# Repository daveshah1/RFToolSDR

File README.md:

# RFTool AD9361 based SDR
RFTool is a standalone AD9361 based SDR with a USB 3 interface and a number of other useful features:

 - AD9361 transceiver IC - dual channel 70MHz-6GHz, up to 54MHz channel bandwidth
 - Xilinx Artix-7 FPGA (XC7A50T-2FTG256I) with 64MBit HyperRAM
 - FT601Q USB 3.0 interface
 - Two LNA inputs (500MHz-3GHz only) and one attenuated input (full AD9361 range)
 - All inputs protected to over +27dBm input
 - Two PA outputs (500MHz-3GHz only) with >20dBm output power and one direct output (full range)
 - Flexible external reference input (switchable termination and coupling)
 - USB powered, no external power needed

Rev 1.0 of the hardware has been built and initial tests completed. Receive-only
FPGA code and a simple Spectrum Analyser application for Linux has also been built.

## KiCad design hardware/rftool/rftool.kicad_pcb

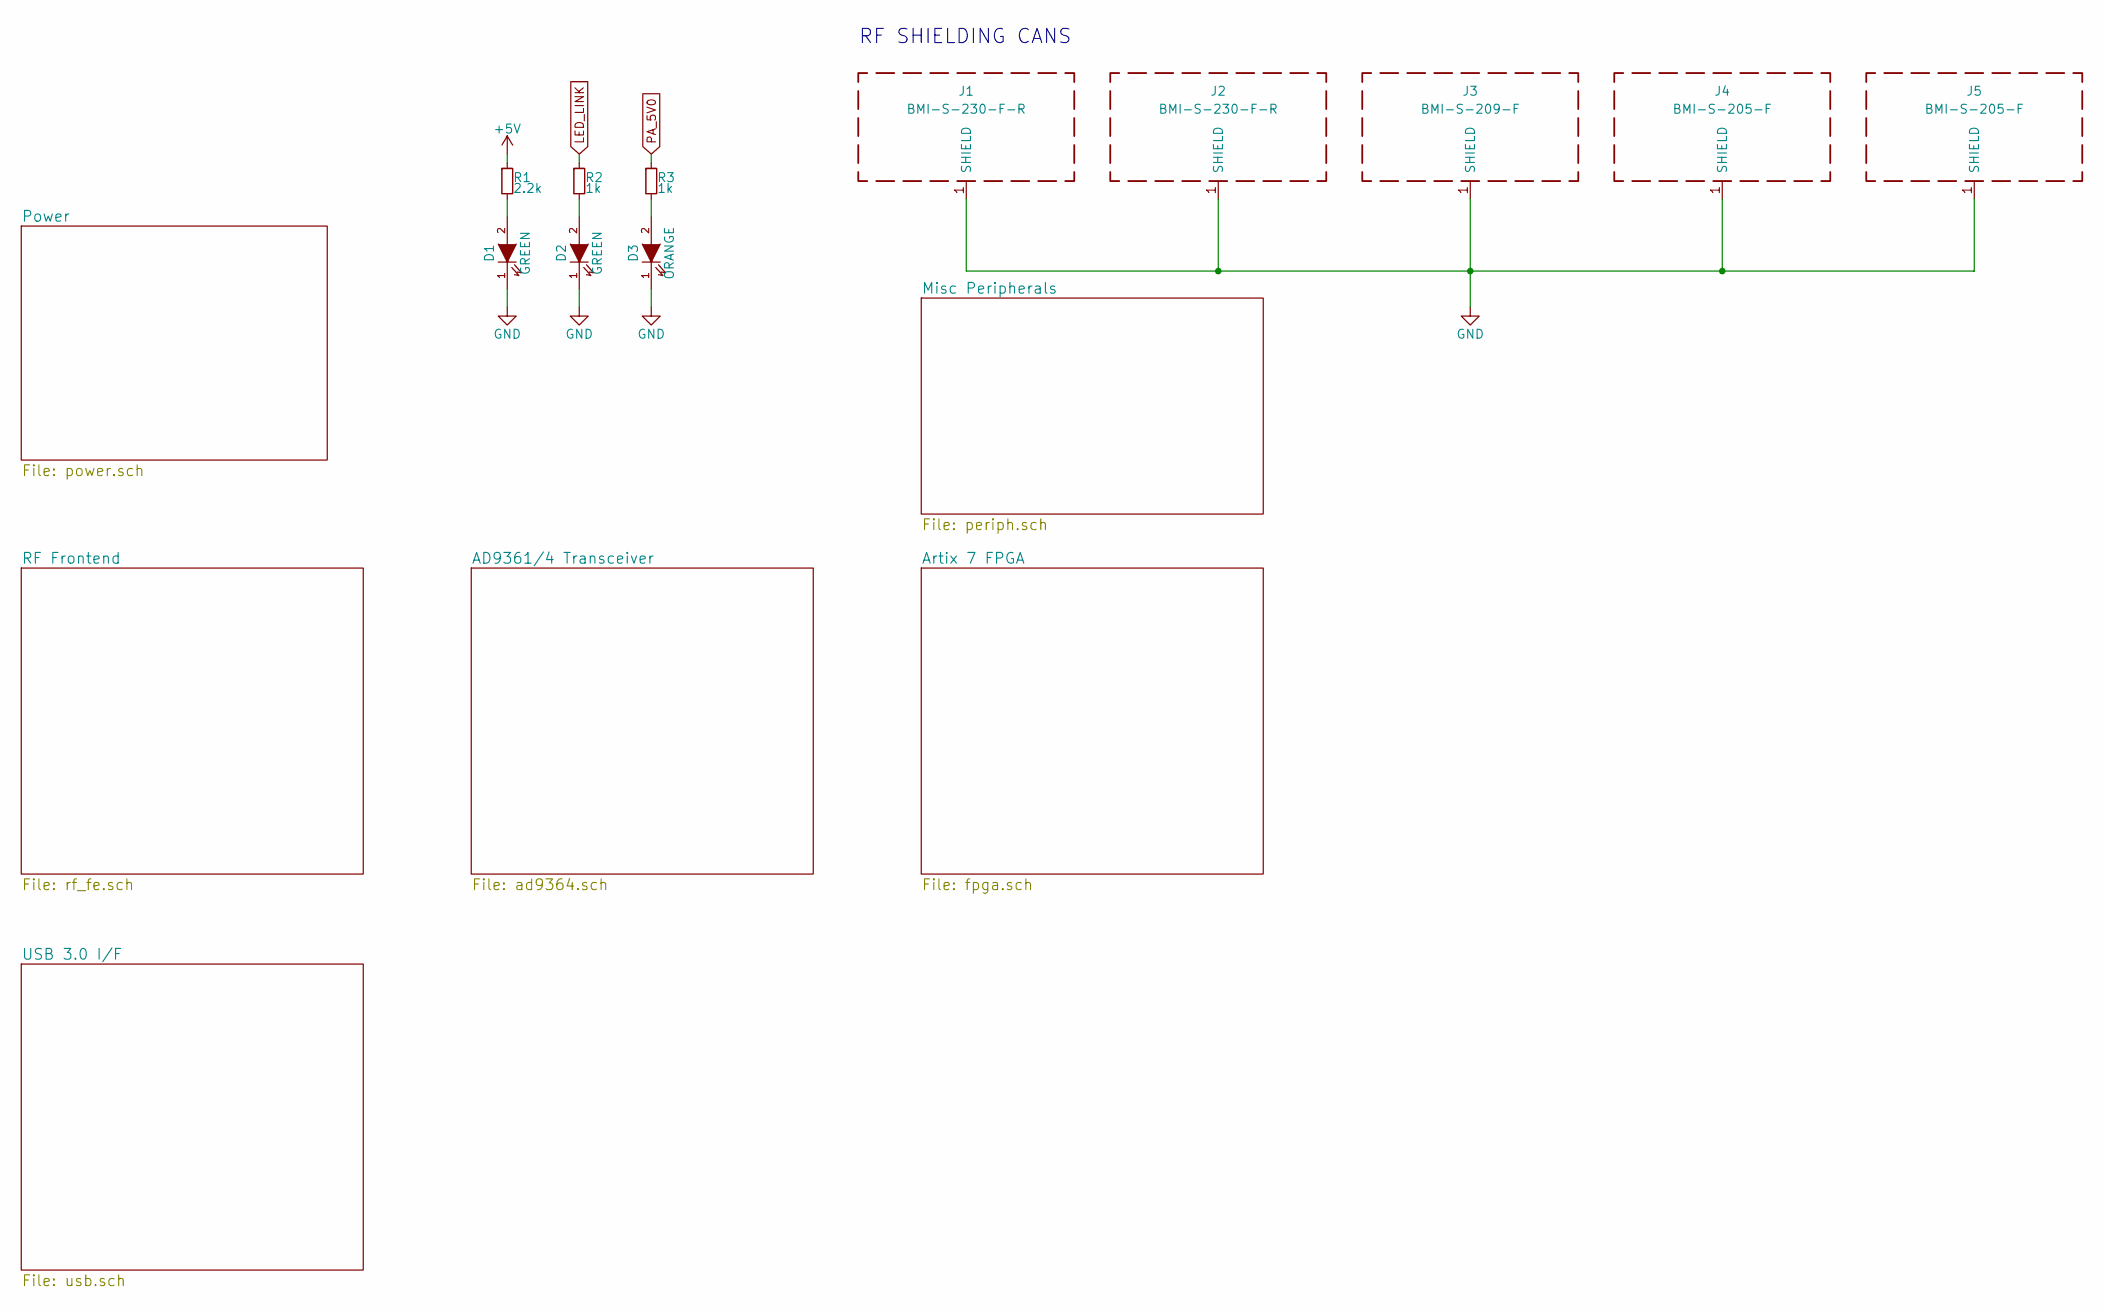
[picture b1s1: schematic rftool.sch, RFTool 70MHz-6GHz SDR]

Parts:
D1, D2: GREEN; LED_0805
D3: ORANGE; LED_0805
J1, J2: BMI-S-230-F-R
J3: BMI-S-209-F
J4, J5: BMI-S-205-F
R1: 2.2k; R_0402
R2, R3: 1k; R_0402

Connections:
+5V: R1.1; also elsewhere on the board
GND: D1.1 (K), D2.1 (K), D3.1 (K), J1.1, J2.1, J3.1, J4.1, J5.1; also elsewhere on the board
LED_LINK: R2.1; also elsewhere on the board
unnamed: D1.2 (A), R1.2
unnamed: D2.2 (A), R2.2
unnamed: D3.2 (A), R3.2
PA_5V0: R3.1; also elsewhere on the board

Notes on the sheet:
RF SHIELDING CANS

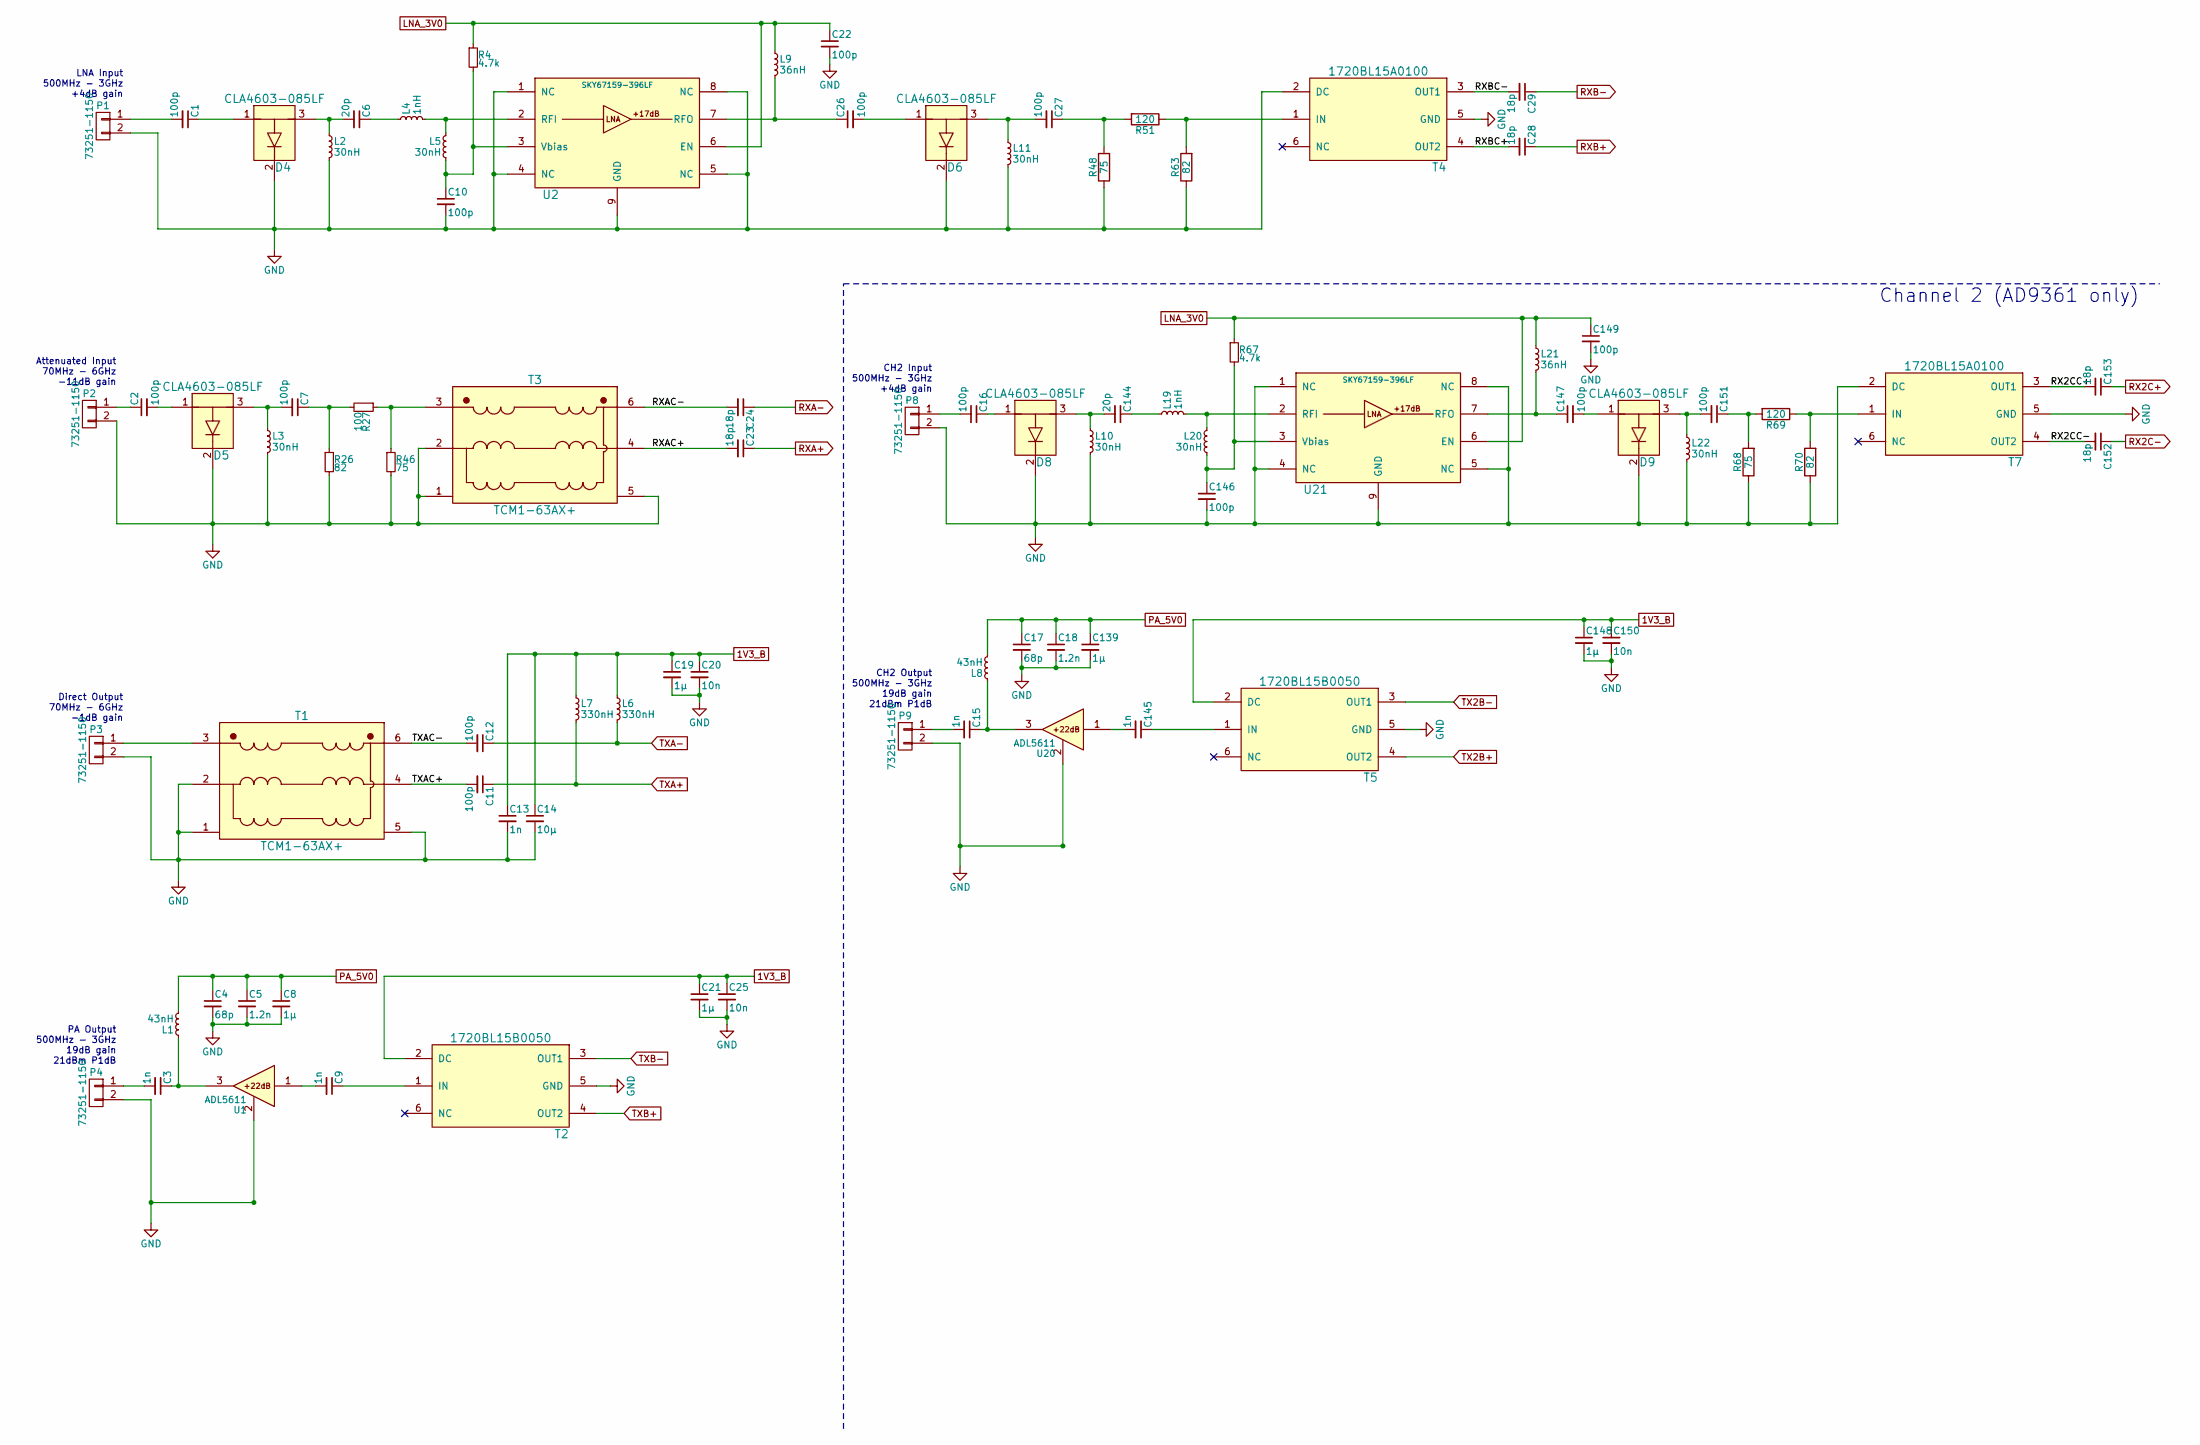
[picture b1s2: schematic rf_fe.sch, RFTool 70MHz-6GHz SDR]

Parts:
C1, C2, C7, C10, C11, C12, C16, C22, C26, C27, C146, C147, C149, C151: 100p; C_0402
C3, C9, C13, C15, C145: 1n; C_0402
C4, C17: 68p; C_0402
C5, C18: 1.2n; C_0402
C6, C144: 20p; C_0402
C8, C19, C21, C139, C148: 1µ; C_0603
C14: 10µ; C_0805
C20, C25, C150: 10n; C_0402
C23, C24, C28, C29, C152, C153: 18p; C_0402
D4, D5, D6, D8, D9: CLA4603-085LF
L1, L8: 43nH; C_0402
L2, L3, L5, L10, L11, L20, L22: 30nH; C_0402
L4, L19: 1nH; C_0402
L6, L7: 330nH; C_0402
L9, L21: 36nH; C_0402
P1, P2, P3, P4, P8, P9: 73251-1150; SMA-EDGE-73251-1150
R4, R67: 4.7k; R_0402
R26, R63, R70: 82; R_0402
R27: 100; R_0402
R46, R48, R68: 75; R_0402
R51, R69: 120; R_0402
T1, T3: TCM1-63AX+
T2, T5: 1720BL15B0050
T4, T7: 1720BL15A0100; 1720BL15B0050
U1, U20: ADL5611; SOT89-3_Housing
U2, U21: SKY67159-396LF; DFN-8-1EP_2x2mm_Pitch0.5mm

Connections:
1V3_B: C13.1, C14.1, C19.1, C20.1, C21.1, C25.1, C148.1, C150.1, L6.1, L7.1, T2.2 (DC), T5.2 (DC); also elsewhere on the board
/RF Frontend/RX2CC+: C153.2, T7.3 (OUT1)
/RF Frontend/RX2CC-: C152.2, T7.4 (OUT2)
/RF Frontend/RXAC+: C23.2, T3.4 (S)
/RF Frontend/RXAC-: C24.2, T3.6 (Sd)
/RF Frontend/RXBC+: C28.2, T4.4 (OUT2)
/RF Frontend/RXBC-: C29.2, T4.3 (OUT1)
/RF Frontend/TXAC+: C11.2, T1.4 (S)
/RF Frontend/TXAC-: C12.2, T1.6 (Sd)
GND: C4.2, C5.2, C8.2, C10.2, C13.2, C14.2, C17.2, C18.2, C19.2, C20.2, C21.2, C22.2, C25.2, C139.2, C146.2, C148.2, C149.2, C150.2, D4.2 (C), D5.2 (C), D6.2 (C), D8.2 (C), D9.2 (C), L2.2, L3.2, L10.2, L11.2, L22.2, P1.2, P2.2, P3.2, P4.2, P8.2, P9.2, R26.2, R46.2, R48.1, R63.1, R68.1, R70.1, T1.1 (NC), T1.2 (p), T1.5 (NC), T2.5 (GND), T3.1 (NC), T3.2 (p), T3.5 (NC), T4.2 (DC), T4.5 (GND), T5.5 (GND), T7.2 (DC), T7.5 (GND), U1.2 (GND), U2.1 (NC), U2.4 (NC), U2.5 (NC), U2.8 (NC), U2.9 (GND), U20.2 (GND), U21.1 (NC), U21.4 (NC), U21.5 (NC), U21.8 (NC), U21.9 (GND); also elsewhere on the board
LNA_3V0: C22.1, C149.1, L9.1, L21.1, R4.1, R67.1, U2.6 (EN), U21.6 (EN); also elsewhere on the board
unnamed: C1.1, D4.1 (A)
unnamed: C1.2, P1.1
unnamed: C2.1, P2.1
unnamed: C2.2, D5.1 (A)
unnamed: C3.1, L1.1, U1.3 (RFOUT)
unnamed: C3.2, P4.1
unnamed: C6.1, L4.1
unnamed: C6.2, D4.3 (A), L2.1
unnamed: C7.1, R26.1, R27.2
unnamed: C7.2, D5.3 (A), L3.1
unnamed: C9.1, T2.1 (IN)
unnamed: C9.2, U1.1 (RFIN)
unnamed: C10.1, L5.2, R4.2, U2.3 (Vbias)
unnamed: C15.1, L8.1, U20.3 (RFOUT)
unnamed: C15.2, P9.1
unnamed: C16.1, D8.1 (A)
unnamed: C16.2, P8.1
unnamed: C26.1, L9.2, U2.7 (RFO)
unnamed: C26.2, D6.1 (A)
unnamed: C27.1, R48.2, R51.2
unnamed: C27.2, D6.3 (A), L11.1
unnamed: C144.1, L19.1
unnamed: C144.2, D8.3 (A), L10.1
unnamed: C145.1, T5.1 (IN)
unnamed: C145.2, U20.1 (RFIN)
unnamed: C146.1, L20.2, R67.2, U21.3 (Vbias)
unnamed: C147.1, L21.2, U21.7 (RFO)
unnamed: C147.2, D9.1 (A)
unnamed: C151.1, R68.2, R69.2
unnamed: C151.2, D9.3 (A), L22.1
unnamed: L4.2, L5.1, U2.2 (RFI)
unnamed: L19.2, L20.1, U21.2 (RFI)
unnamed: P3.1, T1.3 (Pd)
unnamed: R27.1, R46.1, T3.3 (Pd)
unnamed: R51.1, R63.2, T4.1 (IN)
unnamed: R69.1, R70.2, T7.1 (IN)
PA_5V0: C4.1, C5.1, C8.1, C17.1, C18.1, C139.1, L1.2, L8.2; also elsewhere on the board
RX2C+: C153.1; also elsewhere on the board
RX2C-: C152.1; also elsewhere on the board
RXA+: C23.1; also elsewhere on the board
RXA-: C24.1; also elsewhere on the board
RXB+: C28.1; also elsewhere on the board
RXB-: C29.1; also elsewhere on the board
TX2B+: T5.4 (OUT2); also elsewhere on the board
TX2B-: T5.3 (OUT1); also elsewhere on the board
TXA+: C11.1, L7.2; also elsewhere on the board
TXA-: C12.1, L6.2; also elsewhere on the board
TXB+: T2.4 (OUT2); also elsewhere on the board
TXB-: T2.3 (OUT1); also elsewhere on the board

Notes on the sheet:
LNA Input 500MHz - 3GHz +4dB gain
Attenuated Input 70MHz - 6GHz -11dB gain
Direct Output 70MHz - 6GHz -1dB gain
PA Output 500MHz - 3GHz 19dB gain 21dBm P1dB
Channel 2 (AD9361 only)
CH2 Input 500MHz - 3GHz +4dB gain
CH2 Output 500MHz - 3GHz 19dB gain 21dBm P1dB

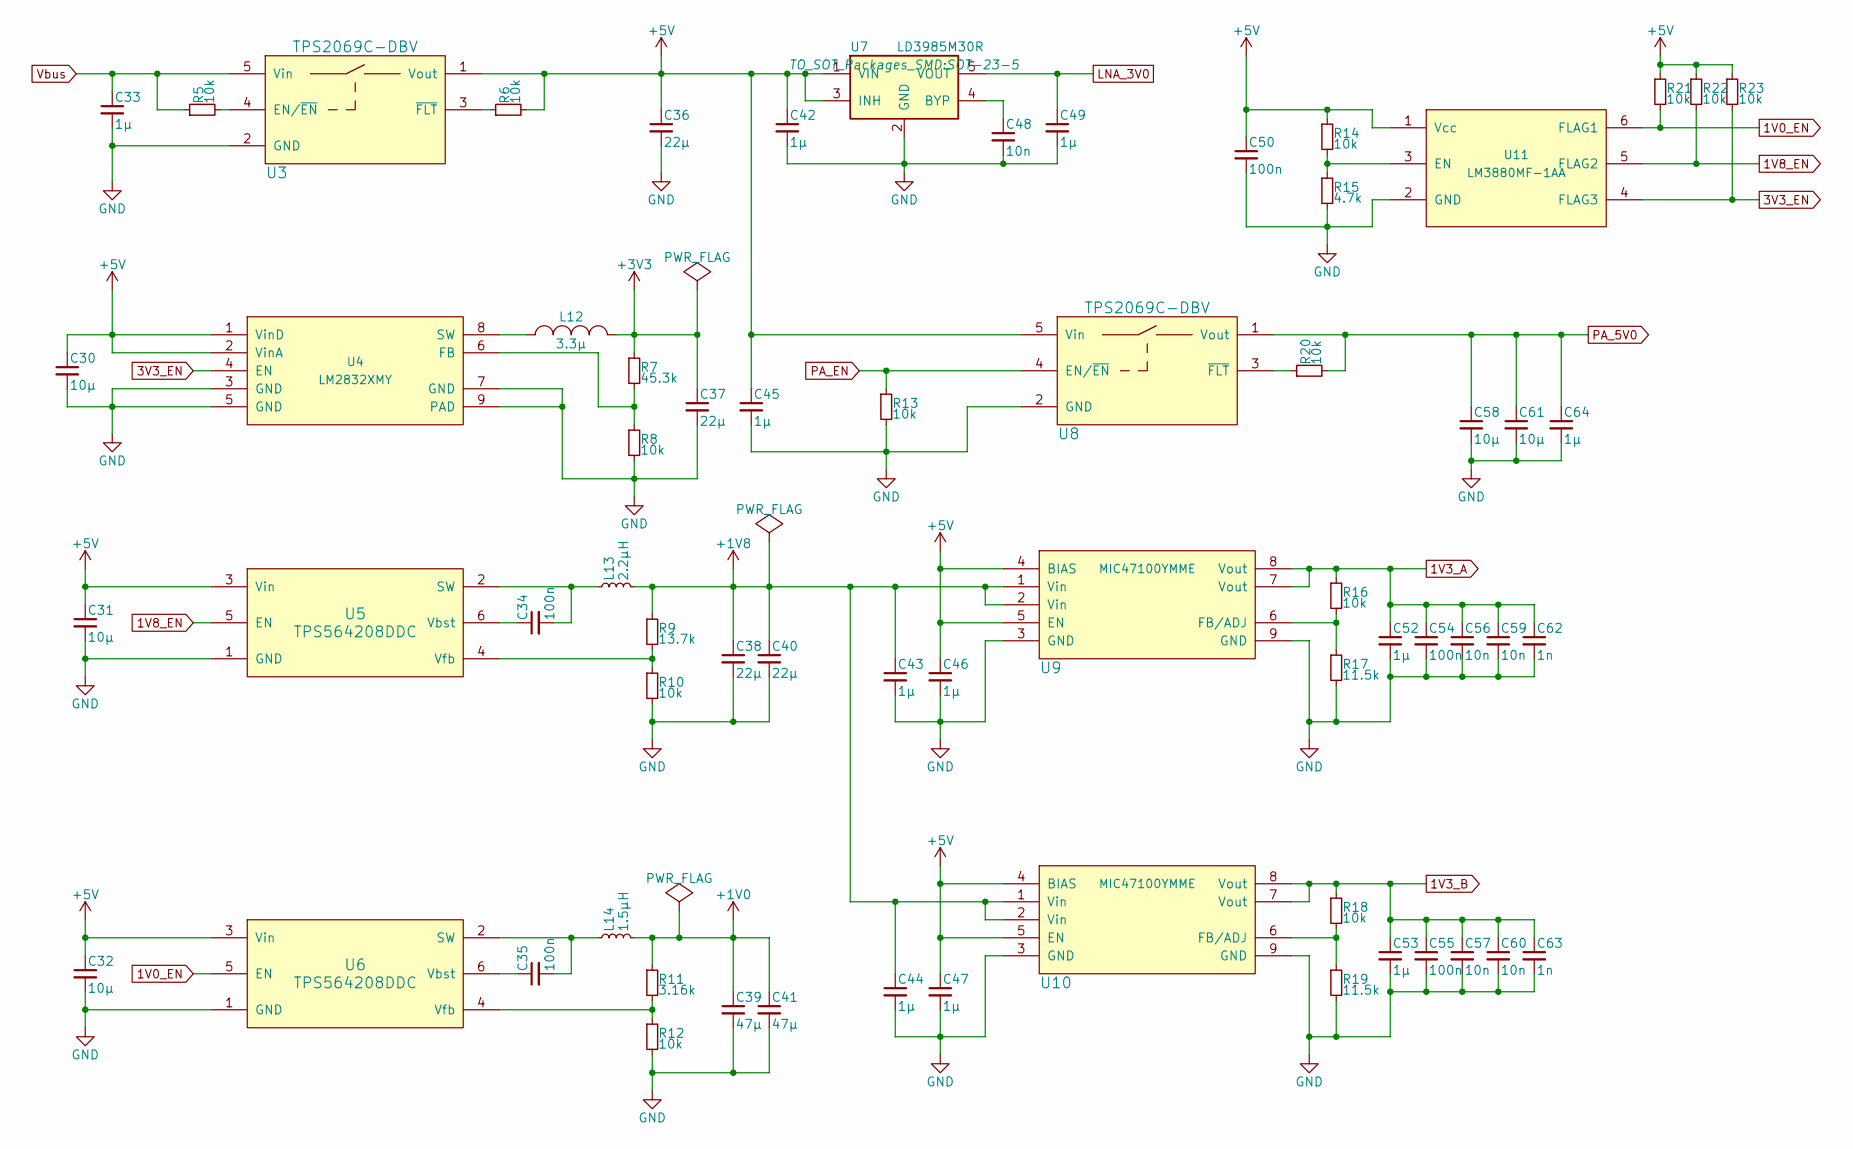
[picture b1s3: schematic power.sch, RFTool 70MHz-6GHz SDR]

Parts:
C30, C31, C32, C58, C61: 10µ; C_0805
C33, C42, C43, C44, C45, C46, C47, C49, C52, C53, C64: 1µ; C_0603
C34, C35, C50, C54, C55: 100n; C_0402
C36, C37, C38, C40: 22µ; C_0805
C39, C41: 47µ; C_1206
C48, C56, C57, C59, C60: 10n; C_0402
C62, C63: 1n; C_0402
L12: 3.3µ; XFL4020
L13: 2.2µH; XFL4020
L14: 1.5µH; XFL4020
R5, R6, R8, R10, R12, R13, R14, R16, R18, R20, R21, R22, R23: 10k; R_0402
R7: 45.3k; R_0402
R9: 13.7k; R_0402
R11: 3.16k; R_0402
R15: 4.7k; R_0402
R17, R19: 11.5k; R_0402
U3, U8: TPS2069C-DBV; SOT-23-5
U4: LM2832XMY; MSOP-8-1EP_3x3mm_Pitch0.65mm
U5, U6: TPS564208DDC; SOT-23-6
U7: LD3985M30R; SOT-23-5
U9, U10: MIC47100YMME; MSOP-8-1EP_3x3mm_Pitch0.65mm
U11: LM3880MF-1AA; SOT-23-6

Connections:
1V0_EN: R21.2, U6.5 (EN), U11.6 (FLAG1)
1V3_A: C52.1, C54.1, C56.1, C59.1, C62.1, R16.1, U9.7 (Vout), U9.8 (Vout); also elsewhere on the board
1V3_B: C53.1, C55.1, C57.1, C60.1, C63.1, R18.1, U10.7 (Vout), U10.8 (Vout); also elsewhere on the board
1V8_EN: R22.2, U5.5 (EN), U11.5 (FLAG2)
3V3_EN: R23.2, U4.4 (EN), U11.4 (FLAG3)
+1V0: C39.1, C41.1, L14.2, R11.1; also elsewhere on the board
+1V8: C38.1, C40.1, C43.1, C44.1, L13.2, R9.1, U9.1 (Vin), U9.2 (Vin), U10.1 (Vin), U10.2 (Vin); also elsewhere on the board
+3V3: C37.1, L12.2, R7.1; also elsewhere on the board
+5V: C30.1, C31.1, C32.1, C36.1, C42.1, C45.1, C46.1, C47.1, C50.1, R6.2, R14.1, R21.1, R22.1, R23.1, U3.1 (Vout), U4.1 (VinD), U4.2 (VinA), U5.3 (Vin), U6.3 (Vin), U7.1 (VIN), U7.3 (INH), U8.5 (Vin), U9.4 (BIAS), U9.5 (EN), U10.4 (BIAS), U10.5 (EN), U11.1 (Vcc); also elsewhere on the board
GND: C30.2, C31.2, C32.2, C33.2, C36.2, C37.2, C38.2, C39.2, C40.2, C41.2, C42.2, C43.2, C44.2, C45.2, C46.2, C47.2, C48.2, C49.2, C50.2, C52.2, C53.2, C54.2, C55.2, C56.2, C57.2, C58.2, C59.2, C60.2, C61.2, C62.2, C63.2, C64.2, R8.2, R10.2, R12.2, R13.2, R15.2, R17.2, R19.2, U3.2 (GND), U4.3 (GND), U4.5 (GND), U4.7 (GND), U4.9 (PAD), U5.1 (GND), U6.1 (GND), U7.2 (GND), U8.2 (GND), U9.3 (GND), U9.9 (GND), U10.3 (GND), U10.9 (GND), U11.2 (GND); also elsewhere on the board
LNA_3V0: C49.1, U7.5 (VOUT); also elsewhere on the board
unnamed: C34.1, U5.6 (Vbst)
unnamed: C34.2, L13.1, U5.2 (SW)
unnamed: C35.1, U6.6 (Vbst)
unnamed: C35.2, L14.1, U6.2 (SW)
unnamed: C48.1, U7.4 (BYP)
unnamed: L12.1, U4.8 (SW)
unnamed: R5.2, U3.4 (EN/~EN)
unnamed: R6.1, U3.3 (~FLT)
unnamed: R7.2, R8.1, U4.6 (FB)
unnamed: R9.2, R10.1, U5.4 (Vfb)
unnamed: R11.2, R12.1, U6.4 (Vfb)
unnamed: R14.2, R15.1, U11.3 (EN)
unnamed: R16.2, R17.1, U9.6 (FB/ADJ)
unnamed: R18.2, R19.1, U10.6 (FB/ADJ)
unnamed: R20.1, U8.3 (~FLT)
PA_5V0: C58.1, C61.1, C64.1, R20.2, U8.1 (Vout); also elsewhere on the board
PA_EN: R13.1, U8.4 (EN/~EN); also elsewhere on the board
Vbus: C33.1, R5.1, U3.5 (Vin); also elsewhere on the board

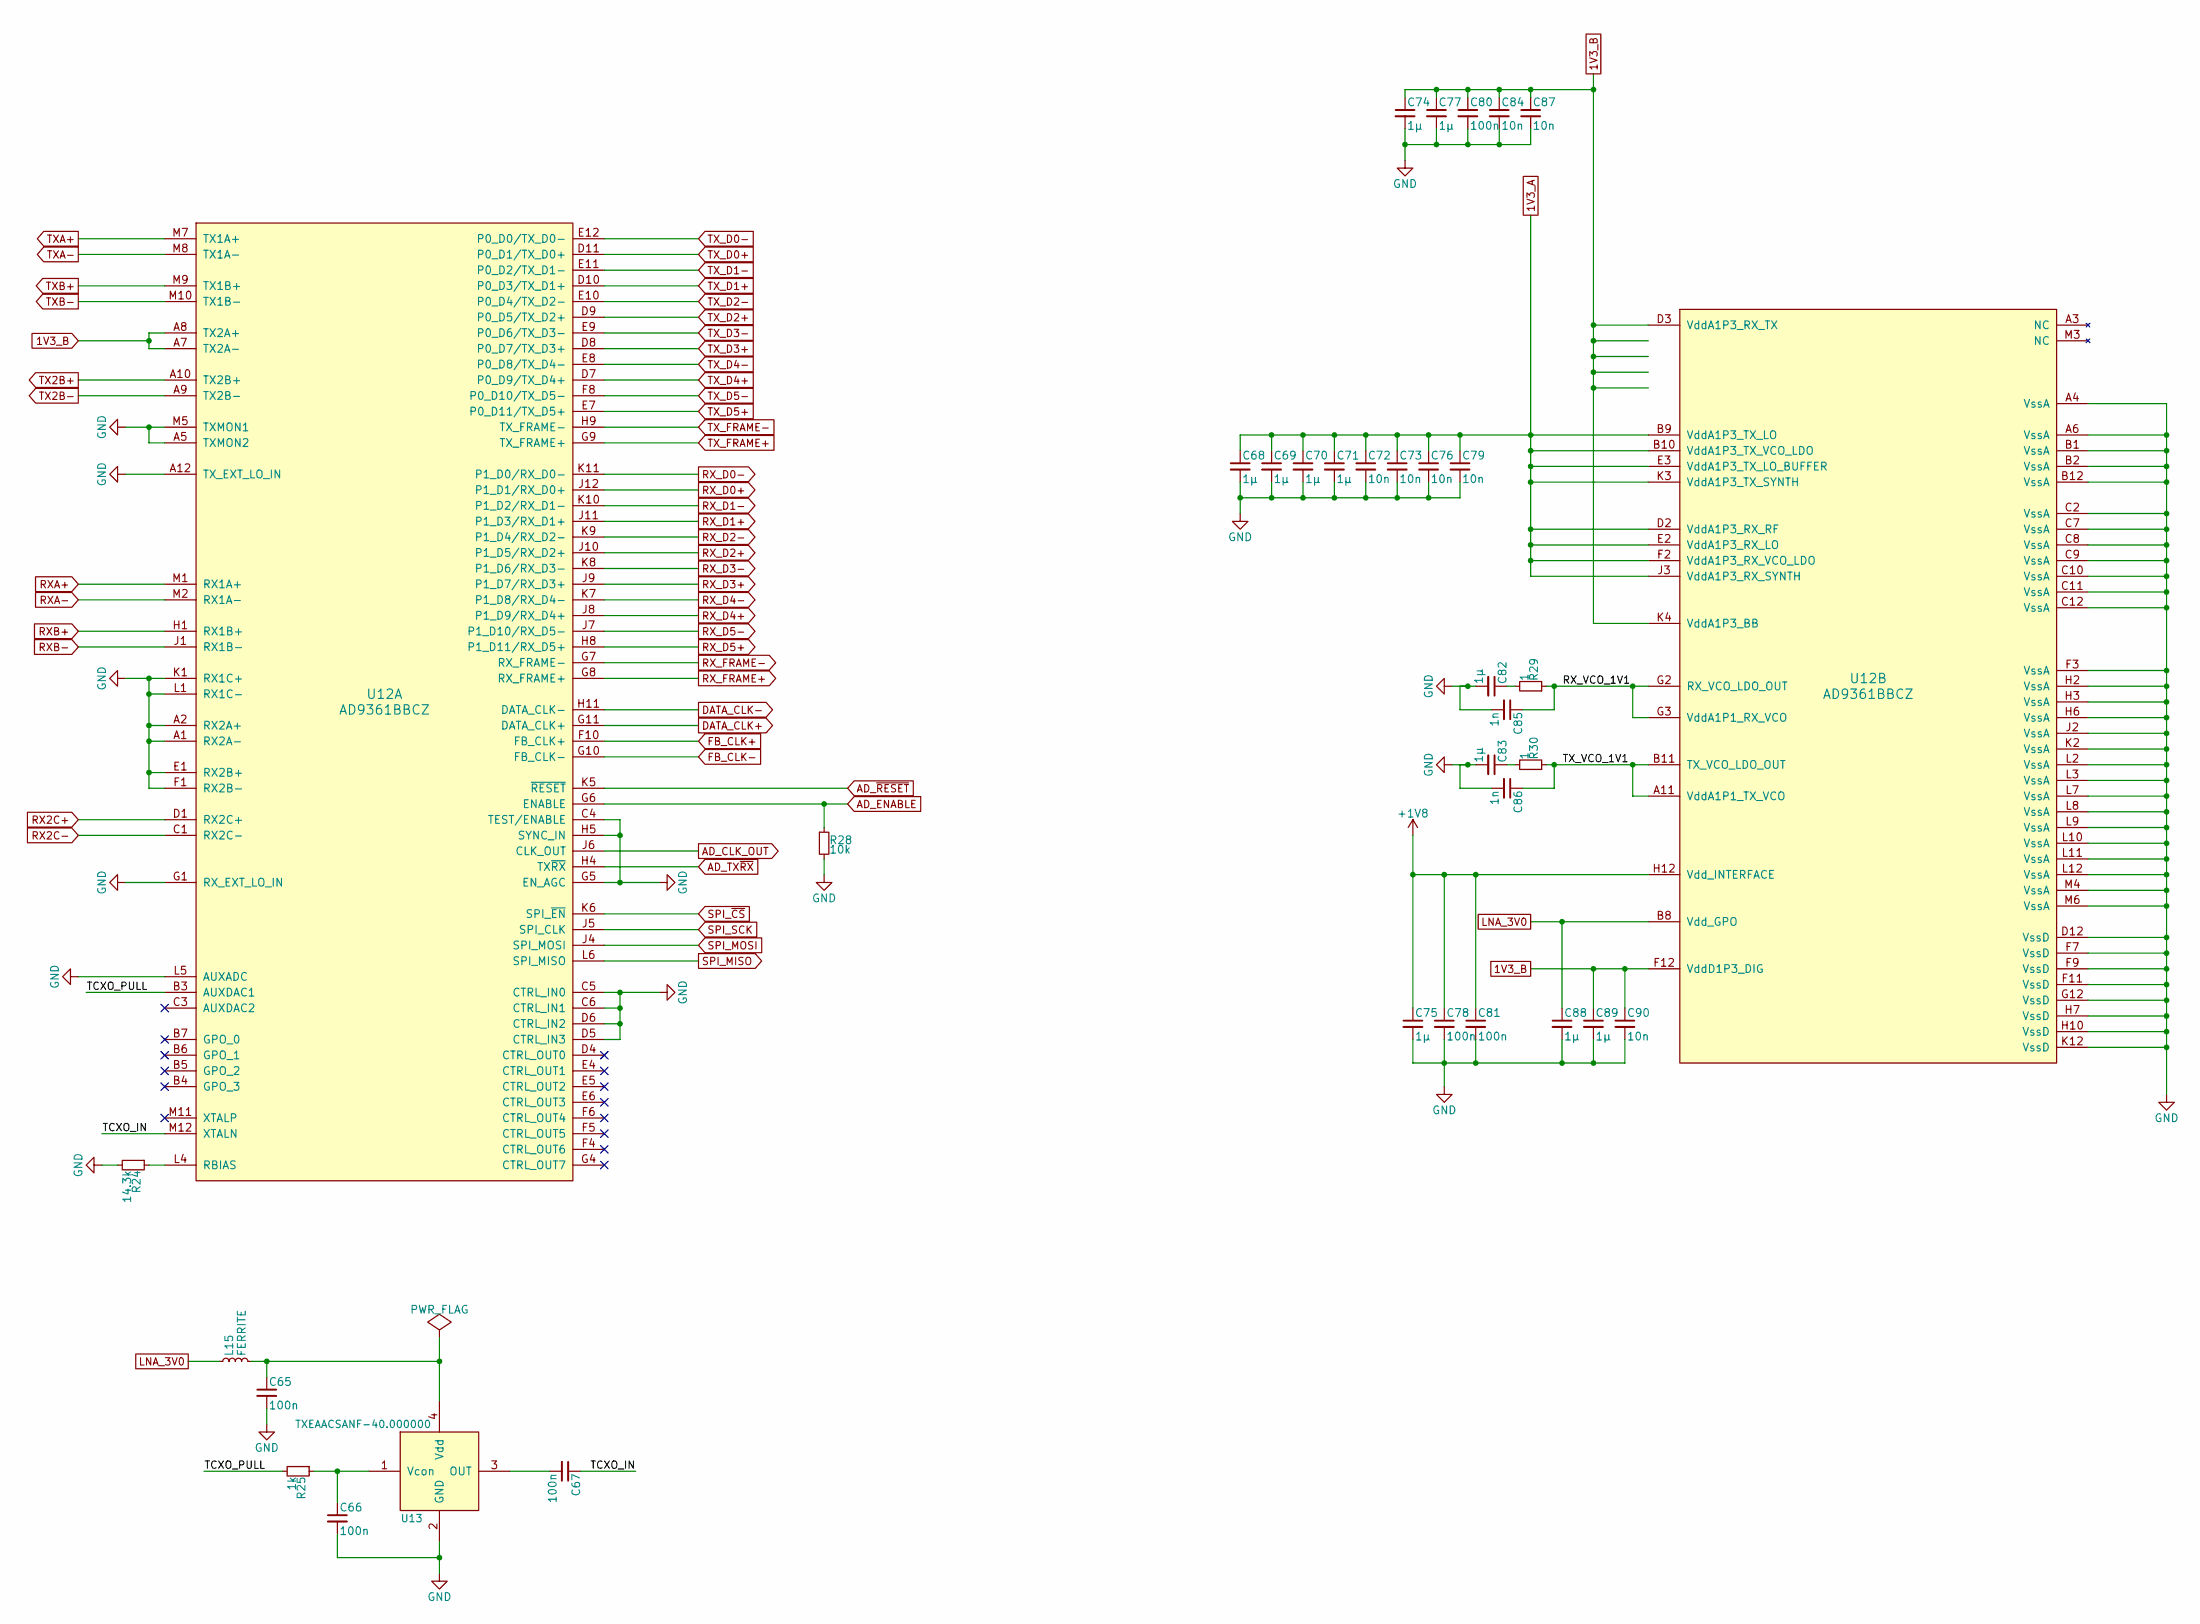
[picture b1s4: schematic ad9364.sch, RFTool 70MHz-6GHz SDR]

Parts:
C65, C66, C67, C78, C80, C81: 100n; C_0402
C68, C69, C70, C71, C74, C75, C77, C82, C83, C88, C89: 1µ; C_0603
C72, C73, C76, C79, C84, C87, C90: 10n; C_0402
C85, C86: 1n; C_0402
L15: FERRITE; C_0805
R24: 14.3k; R_0402
R25: 1k; R_0402
R28: 10k; R_0402
R29, R30: 1; R_0402
U12: AD9361BBCZ; CSP_BGA_144_pitch0.8mm
U13: TXEAACSANF-40.000000; VCTCXO_TX_3.2x2.5mm

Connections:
1V3_A: C68.1, C69.1, C70.1, C71.1, C72.1, C73.1, C76.1, C79.1, U12.B9 (VddA1P3_TX_LO), U12.B10 (VddA1P3_TX_VCO_LDO), U12.D2 (VddA1P3_RX_RF), U12.E2 (VddA1P3_RX_LO), U12.E3 (VddA1P3_TX_LO_BUFFER), U12.F2 (VddA1P3_RX_VCO_LDO), U12.J3 (VddA1P3_RX_SYNTH), U12.K3 (VddA1P3_TX_SYNTH); also elsewhere on the board
1V3_B: C74.1, C77.1, C80.1, C84.1, C87.1, C89.1, C90.1, U12.A7 (TX2A-), U12.A8 (TX2A+), U12.D3 (VddA1P3_RX_TX), U12.F12 (VddD1P3_DIG), U12.K4 (VddA1P3_BB); also elsewhere on the board
+1V8: C75.1, C78.1, C81.1, U12.H12 (Vdd_INTERFACE); also elsewhere on the board
/AD9361/4 Transceiver/RX_VCO_1V1: C85.1, R29.1, U12.G2 (RX_VCO_LDO_OUT), U12.G3 (VddA1P1_RX_VCO)
/AD9361/4 Transceiver/TCXO_IN: C67.1, U12.M12 (XTALN)
/AD9361/4 Transceiver/TCXO_PULL: R25.2, U12.B3 (AUXDAC1)
/AD9361/4 Transceiver/TX_VCO_1V1: C86.1, R30.1, U12.A11 (VddA1P1_TX_VCO), U12.B11 (TX_VCO_LDO_OUT)
AD_CLK_OUT: U12.J6 (CLK_OUT); also elsewhere on the board
AD_ENABLE: R28.1, U12.G6 (ENABLE); also elsewhere on the board
AD_TX~RX: U12.H4 (TX~RX); also elsewhere on the board
AD_~RESET: U12.K5 (~RESET); also elsewhere on the board
DATA_CLK+: U12.G11 (DATA_CLK+); also elsewhere on the board
DATA_CLK-: U12.H11 (DATA_CLK-); also elsewhere on the board
FB_CLK+: U12.F10 (FB_CLK+); also elsewhere on the board
FB_CLK-: U12.G10 (FB_CLK-); also elsewhere on the board
GND: C65.2, C66.2, C68.2, C69.2, C70.2, C71.2, C72.2, C73.2, C74.2, C75.2, C76.2, C77.2, C78.2, C79.2, C80.2, C81.2, C82.2, C83.2, C84.2, C85.2, C86.2, C87.2, C88.2, C89.2, C90.2, R24.2, R28.2, U12.A1 (RX2A-), U12.A2 (RX2A+), U12.A4 (VssA), U12.A5 (TXMON2), U12.A6 (VssA), U12.A12 (TX_EXT_LO_IN), U12.B1 (VssA), U12.B2 (VssA), U12.B12 (VssA), U12.C2 (VssA), U12.C4 (TEST/ENABLE), U12.C5 (CTRL_IN0), U12.C6 (CTRL_IN1), U12.C7 (VssA), U12.C8 (VssA), U12.C9 (VssA), U12.C10 (VssA), U12.C11 (VssA), U12.C12 (VssA), U12.D5 (CTRL_IN3), U12.D6 (CTRL_IN2), U12.D12 (VssD), U12.E1 (RX2B+), U12.F1 (RX2B-), U12.F3 (VssA), U12.F7 (VssD), U12.F9 (VssD), U12.F11 (VssD), U12.G1 (RX_EXT_LO_IN), U12.G5 (EN_AGC), U12.G12 (VssD), U12.H2 (VssA), U12.H3 (VssA), U12.H5 (SYNC_IN), U12.H6 (VssA), U12.H7 (VssD), U12.H10 (VssD), U12.J2 (VssA), U12.K1 (RX1C+), U12.K2 (VssA), U12.K12 (VssD), U12.L1 (RX1C-), U12.L2 (VssA), U12.L3 (VssA), U12.L5 (AUXADC), U12.L7 (VssA), U12.L8 (VssA), U12.L9 (VssA), U12.L10 (VssA), U12.L11 (VssA), U12.L12 (VssA), U12.M4 (VssA), U12.M5 (TXMON1), U12.M6 (VssA), U13.2 (GND); also elsewhere on the board
LNA_3V0: C88.1, L15.1, U12.B8 (Vdd_GPO); also elsewhere on the board
unnamed: C65.1, L15.2, U13.4 (Vdd)
unnamed: C66.1, R25.1, U13.1 (Vcon)
unnamed: C67.2, U13.3 (OUT)
unnamed: C82.1, R29.2
unnamed: C83.1, R30.2
unnamed: R24.1, U12.L4 (RBIAS)
RX2C+: U12.D1 (RX2C+); also elsewhere on the board
RX2C-: U12.C1 (RX2C-); also elsewhere on the board
RXA+: U12.M1 (RX1A+); also elsewhere on the board
RXA-: U12.M2 (RX1A-); also elsewhere on the board
RXB+: U12.H1 (RX1B+); also elsewhere on the board
RXB-: U12.J1 (RX1B-); also elsewhere on the board
RX_D0+: U12.J12 (P1_D1/RX_D0+); also elsewhere on the board
RX_D0-: U12.K11 (P1_D0/RX_D0-); also elsewhere on the board
RX_D1+: U12.J11 (P1_D3/RX_D1+); also elsewhere on the board
RX_D1-: U12.K10 (P1_D2/RX_D1-); also elsewhere on the board
RX_D2+: U12.J10 (P1_D5/RX_D2+); also elsewhere on the board
RX_D2-: U12.K9 (P1_D4/RX_D2-); also elsewhere on the board
RX_D3+: U12.J9 (P1_D7/RX_D3+); also elsewhere on the board
RX_D3-: U12.K8 (P1_D6/RX_D3-); also elsewhere on the board
RX_D4+: U12.J8 (P1_D9/RX_D4+); also elsewhere on the board
RX_D4-: U12.K7 (P1_D8/RX_D4-); also elsewhere on the board
RX_D5+: U12.H8 (P1_D11/RX_D5+); also elsewhere on the board
RX_D5-: U12.J7 (P1_D10/RX_D5-); also elsewhere on the board
RX_FRAME+: U12.G8 (RX_FRAME+); also elsewhere on the board
RX_FRAME-: U12.G7 (RX_FRAME-); also elsewhere on the board
SPI_MISO: U12.L6 (SPI_MISO); also elsewhere on the board
SPI_MOSI: U12.J4 (SPI_MOSI); also elsewhere on the board
SPI_SCK: U12.J5 (SPI_CLK); also elsewhere on the board
SPI_~CS: U12.K6 (SPI_~EN); also elsewhere on the board
TX2B+: U12.A10 (TX2B+); also elsewhere on the board
TX2B-: U12.A9 (TX2B-); also elsewhere on the board
TXA+: U12.M7 (TX1A+); also elsewhere on the board
TXA-: U12.M8 (TX1A-); also elsewhere on the board
TXB+: U12.M9 (TX1B+); also elsewhere on the board
TXB-: U12.M10 (TX1B-); also elsewhere on the board
TX_D0+: U12.D11 (P0_D1/TX_D0+); also elsewhere on the board
TX_D0-: U12.E12 (P0_D0/TX_D0-); also elsewhere on the board
TX_D1+: U12.D10 (P0_D3/TX_D1+); also elsewhere on the board
TX_D1-: U12.E11 (P0_D2/TX_D1-); also elsewhere on the board
TX_D2+: U12.D9 (P0_D5/TX_D2+); also elsewhere on the board
TX_D2-: U12.E10 (P0_D4/TX_D2-); also elsewhere on the board
TX_D3+: U12.D8 (P0_D7/TX_D3+); also elsewhere on the board
TX_D3-: U12.E9 (P0_D6/TX_D3-); also elsewhere on the board
TX_D4+: U12.D7 (P0_D9/TX_D4+); also elsewhere on the board
TX_D4-: U12.E8 (P0_D8/TX_D4-); also elsewhere on the board
TX_D5+: U12.E7 (P0_D11/TX_D5+); also elsewhere on the board
TX_D5-: U12.F8 (P0_D10/TX_D5-); also elsewhere on the board
TX_FRAME+: U12.G9 (TX_FRAME+); also elsewhere on the board
TX_FRAME-: U12.H9 (TX_FRAME-); also elsewhere on the board

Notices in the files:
hardware/rftool/ad9364.sch:
CC-BY-SA
